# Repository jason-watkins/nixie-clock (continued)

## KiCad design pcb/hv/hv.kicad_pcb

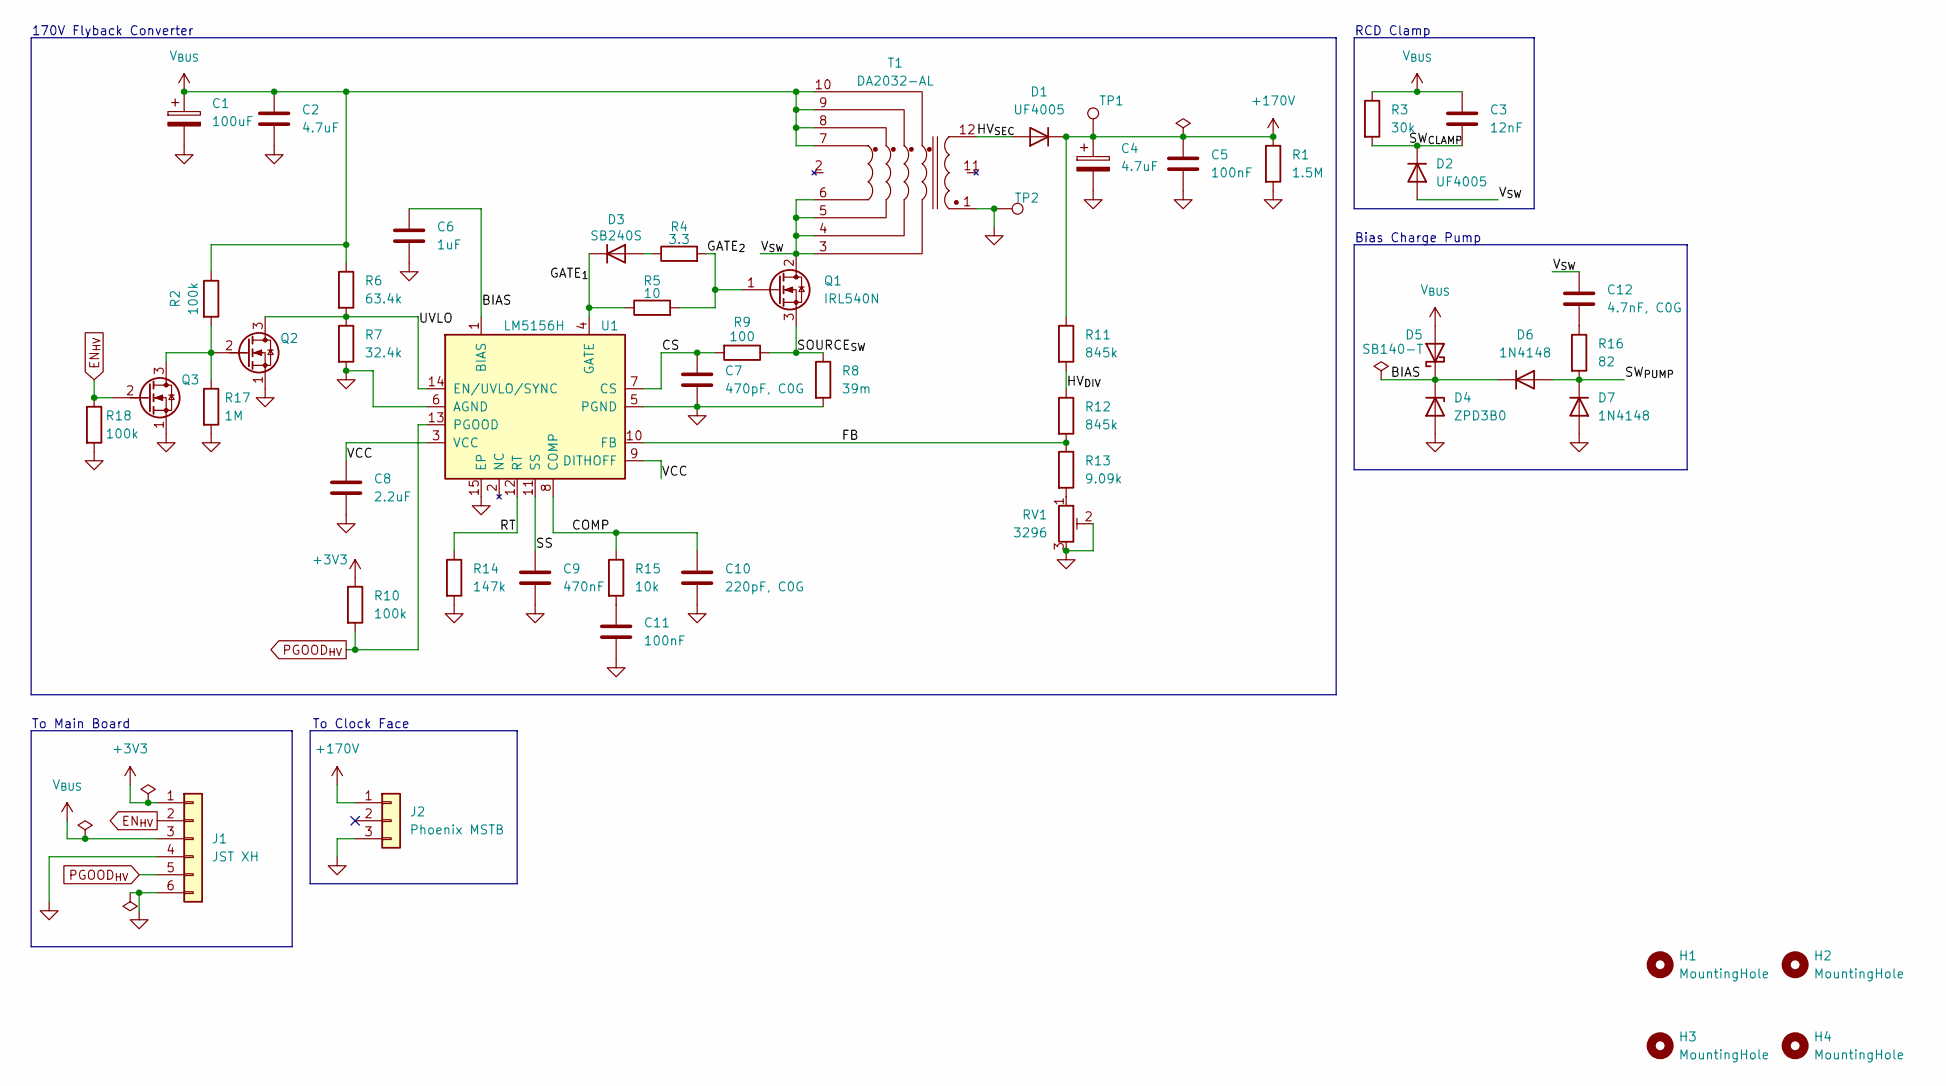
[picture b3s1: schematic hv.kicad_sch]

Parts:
C1: 100uF; CP_Radial_D8.0mm_P3.50mm; MFG Part No A750KK107M1EAAE040
C2: 4.7uF; C_Rect_L5.1mm_W3.2mm_P5.08mm_Goldmax; MFG Part No C322C475K5R5TA
C3: 12nF; C_Rect_L7.2mm_W2.5mm_P5.00mm_PHE426; MFG Part No PHE426DJ5120JR05
C4: 4.7uF; CP_Radial_D8.0mm_P3.50mm; MFG Part No A759KS475M2EAAE496
C5: 100nF; C_Rect_L7.9mm_W5.9mm_P5.00mm_ECQE; MFG Part No ECQ-E2104KB
C6: 1uF; C_Rect_L7.1mm_W4.1mm_P5.08mm_Goldmax; MFG Part No C330C105K5R5TA7303
C7: 470pF, C0G; C_Rect_L3.8mm_W2.5mm_P2.54mm_Goldmax; MFG Part No C315C471J1G5TA
C8: 2.2uF; C_Axial_L5.1mm_D3.1mm_P7.50mm_Horizontal; MFG Part No C410C225K3R5TA
C9: 470nF; C_Rect_L5.1mm_W3.2mm_P5.08mm_Goldmax; MFG Part No C322C474K5R5TA7301
C10: 220pF, C0G; C_Rect_L5.1mm_W3.2mm_P5.08mm_Goldmax; MFG Part No C322C221J2G5TA
C11: 100nF; C_Rect_L5.1mm_W3.2mm_P5.08mm_Goldmax; MFG Part No C322C104K5R5TA
C12: 4.7nF, C0G; C_Rect_L3.8mm_W2.5mm_P2.54mm_Goldmax; MFG Part No C315C472J2G5TA
D1: UF4005; D_DO-41_SOD81_P10.16mm_Horizontal; MFG Part No UF4005
D2: UF4005; D_DO-41_SOD81_P7.62mm_Horizontal; MFG Part No UF4005
D3: SB240S; D_DO-41_SOD81_P7.62mm_Horizontal; MFG Part No SB240S-E3/54
D4: ZPD3B0; D_DO-35_SOD27_P7.62mm_Horizontal; MFG Part No ZPD3B0
D5: SB140-T; D_DO-41_SOD81_P7.62mm_Horizontal; MFG Part No SB140-T
D6, D7: 1N4148; D_DO-35_SOD27_P7.62mm_Horizontal; MFG Part No 1N4148TR
H1, H2, H3, H4: MountingHole; MountingHole_3.2mm_M3_ISO7380
J1: JST XH; JST_XH_S6B-XH-A_1x06_P2.50mm_Horizontal; MFG Part No S6B-XH-A
J2: Phoenix MSTB; PhoenixContact_MSTBA_2,5_3-G-5,08_1x03_P5.08mm_Horizontal; MFG Part No 1757255
Q1: IRL540N; TO-220-3_Vertical; MFG Part No IRL540NPBF
Q2, Q3: TN2106N3-G; TO-92L; MFG Part No TN2106N3-G
R1: 1.5M; R_Axial_DIN0309_L9.0mm_D3.2mm_P12.70mm_Horizontal; MFG Part No CFR-50JB-52-1M5
R2, R10, R18: 100k; R_Axial_DIN0204_L3.6mm_D1.6mm_P5.08mm_Horizontal; MFG Part No CFR-12JB-52-100K
R3: 30k; R_Axial_DIN0207_L6.3mm_D2.5mm_P7.62mm_Horizontal; MFG Part No CFR-25JB-52-30K
R4: 3.3; R_Axial_DIN0204_L3.6mm_D1.6mm_P5.08mm_Horizontal; MFG Part No CFR-12JB-52-3R3
R5: 10; R_Axial_DIN0204_L3.6mm_D1.6mm_P5.08mm_Horizontal; MFG Part No CFR25SJT-52-10R
R6: 63.4k; R_Axial_DIN0207_L6.3mm_D2.5mm_P7.62mm_Horizontal; MFG Part No MFR-25FRF52-63K4
R7: 32.4k; R_Axial_DIN0207_L6.3mm_D2.5mm_P7.62mm_Horizontal; MFG Part No MFR-25FRF52-32K4
R8: 39m; R_2512_6332Metric_Pad1.40x3.35mm_HandSolder; MFG Part No TLRP3A20WR039FTE
R9: 100; R_Axial_DIN0204_L3.6mm_D1.6mm_P5.08mm_Horizontal; MFG Part No CFR25SJT-52-100R
R11, R12: 845k; R_Axial_DIN0207_L6.3mm_D2.5mm_P7.62mm_Horizontal; MFG Part No MFR-25FBF52-845K
R13: 9.09k; R_Axial_DIN0207_L6.3mm_D2.5mm_P7.62mm_Horizontal; MFG Part No MFR-25FBF52-9K09
R14: 147k; R_Axial_DIN0207_L6.3mm_D2.5mm_P7.62mm_Horizontal; MFG Part No MFR-25FRF52-147K
R15: 10k; R_Axial_DIN0204_L3.6mm_D1.6mm_P5.08mm_Horizontal; MFG Part No CFR-12JB-52-10K
R16: 82; R_Axial_DIN0309_L9.0mm_D3.2mm_P12.70mm_Horizontal; MFG Part No CFR-50JB-52-82R
R17: 1M; R_Axial_DIN0204_L3.6mm_D1.6mm_P5.08mm_Horizontal; MFG Part No CFR-12JB-52-1M
RV1: 3296; Potentiometer_Bourns_3296W_Vertical; MFG Part No 3296W-1-202LF
T1: DA2032-AL; MFG Part No DA2032-AL
TP1: +170V; TestPoint_Keystone_5000-5004_Miniature; MFG Part No 5001
TP2: GND; TestPoint_Keystone_5000-5004_Miniature; MFG Part No 5000
U1: LM5156H; Texas_HTSSOP-14-1EP_4.4x5mm_P0.65mm_EP3.4x5mm_Mask3.155x3.2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; MFG Part No LM51561HPWPR

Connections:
+3V3: J1.1, R10.1
+170V: C4.1, C5.1, D1.1 (K), J2.1, R1.1, R11.1, TP1.1 (1_1)
/BIAS: C6.2, D4.1 (K), D5.1 (K), D6.1 (K), U1.1 (BIAS)
/COMP: C10.2, R15.1, U1.8 (COMP)
/CS: C7.2, R9.2, U1.7 (CS)
/FB: R12.2, R13.1, U1.10 (FB)
/GATE_{1}: D3.1 (K), R5.1, U1.4 (GATE)
/GATE_{2}: Q1.1 (G), R4.2, R5.2
/HV_{DIV}: R11.2, R12.1
/HV_{SEC}: D1.2 (A), T1.12
/RT: R14.1, U1.12 (RT)
/SOURCE_{SW}: Q1.3 (S), R8.1, R9.1
/SS: C9.2, U1.11 (SS)
/SW_{CLAMP}: C3.1, D2.1 (K), R3.2
/SW_{PUMP}: D6.2 (A), D7.1 (K), R16.2
/UVLO: Q2.3 (D), R6.2, R7.1, U1.14 (EN/UVLO/SYNC)
/VCC: C8.2, U1.3 (VCC), U1.9 (DITHOFF)
/V_{SW}: C12.1, D2.2 (A), Q1.2 (D), T1.3, T1.4, T1.5, T1.6
EN_{HV}: J1.2, Q3.2 (G), R18.1
GND: C1.2, C2.2, C4.2, C5.2, C6.1, C7.1, C8.1, C9.1, C10.1, C11.1, D4.2 (A), D7.2 (A), J1.4, J1.6, J2.3, Q2.1 (S), Q3.1 (S), R1.2, R7.2, R8.2, R14.2, R17.2, R18.2, RV1.2, RV1.3, T1.1, TP2.1 (1_1), U1.5 (PGND), U1.6 (AGND), U1.15 (EP)
unnamed: C11.2, R15.2
unnamed: C12.2, R16.1
unnamed: D3.2 (A), R4.1
unnamed: Q2.2 (G), Q3.3 (D), R2.2, R17.1
unnamed: R13.2, RV1.1
PGOOD_{HV}: J1.5, R10.2, U1.13 (PGOOD)
V_{BUS}: C1.1, C2.1, C3.2, D5.2 (A), J1.3, R2.1, R3.1, R6.1, T1.7, T1.8, T1.9, T1.10

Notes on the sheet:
To Main Board
To Clock Face
Bias Charge Pump
RCD Clamp
170V Flyback Converter

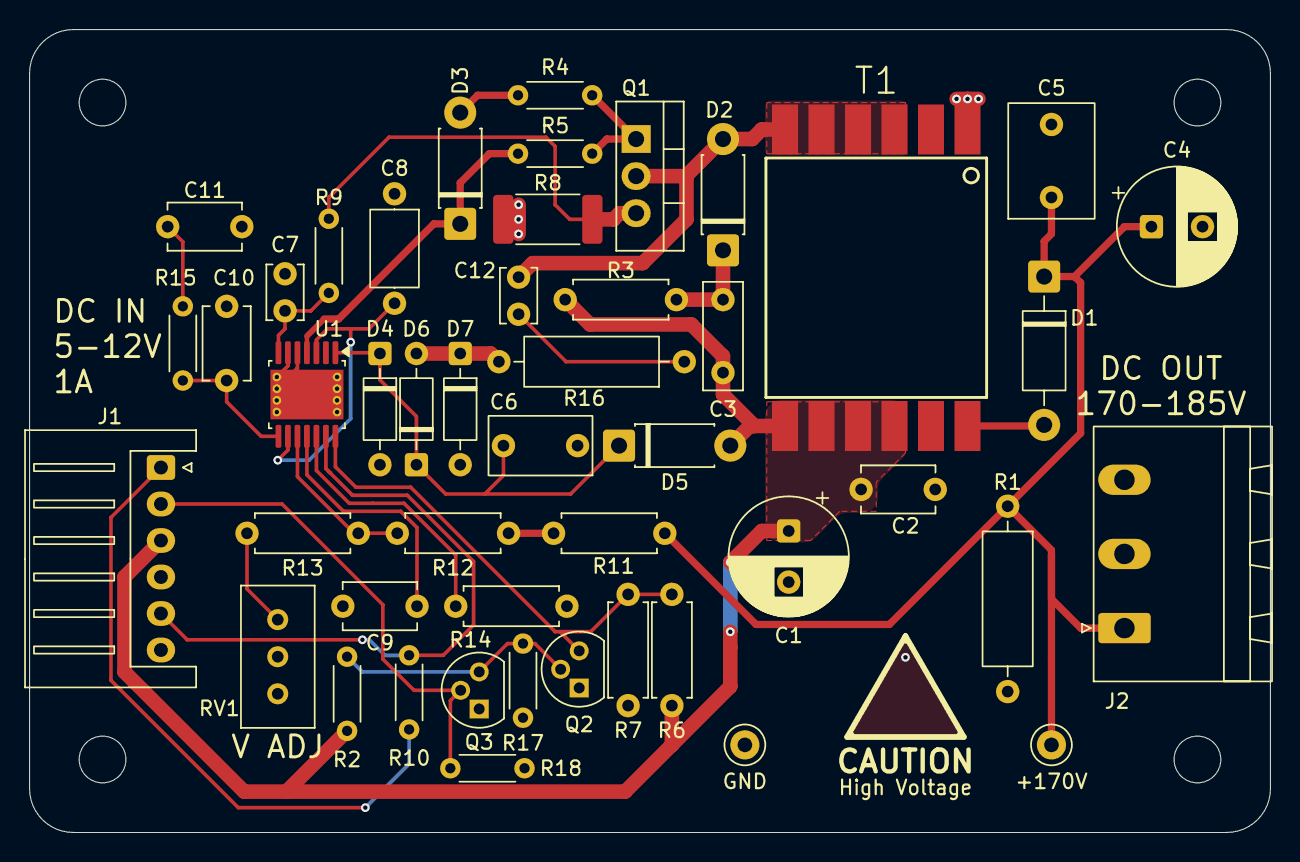
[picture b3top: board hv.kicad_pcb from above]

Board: 2 copper layers, 85.0 x 55.0 mm, 51 parts (0 on the bottom side), 27 nets.

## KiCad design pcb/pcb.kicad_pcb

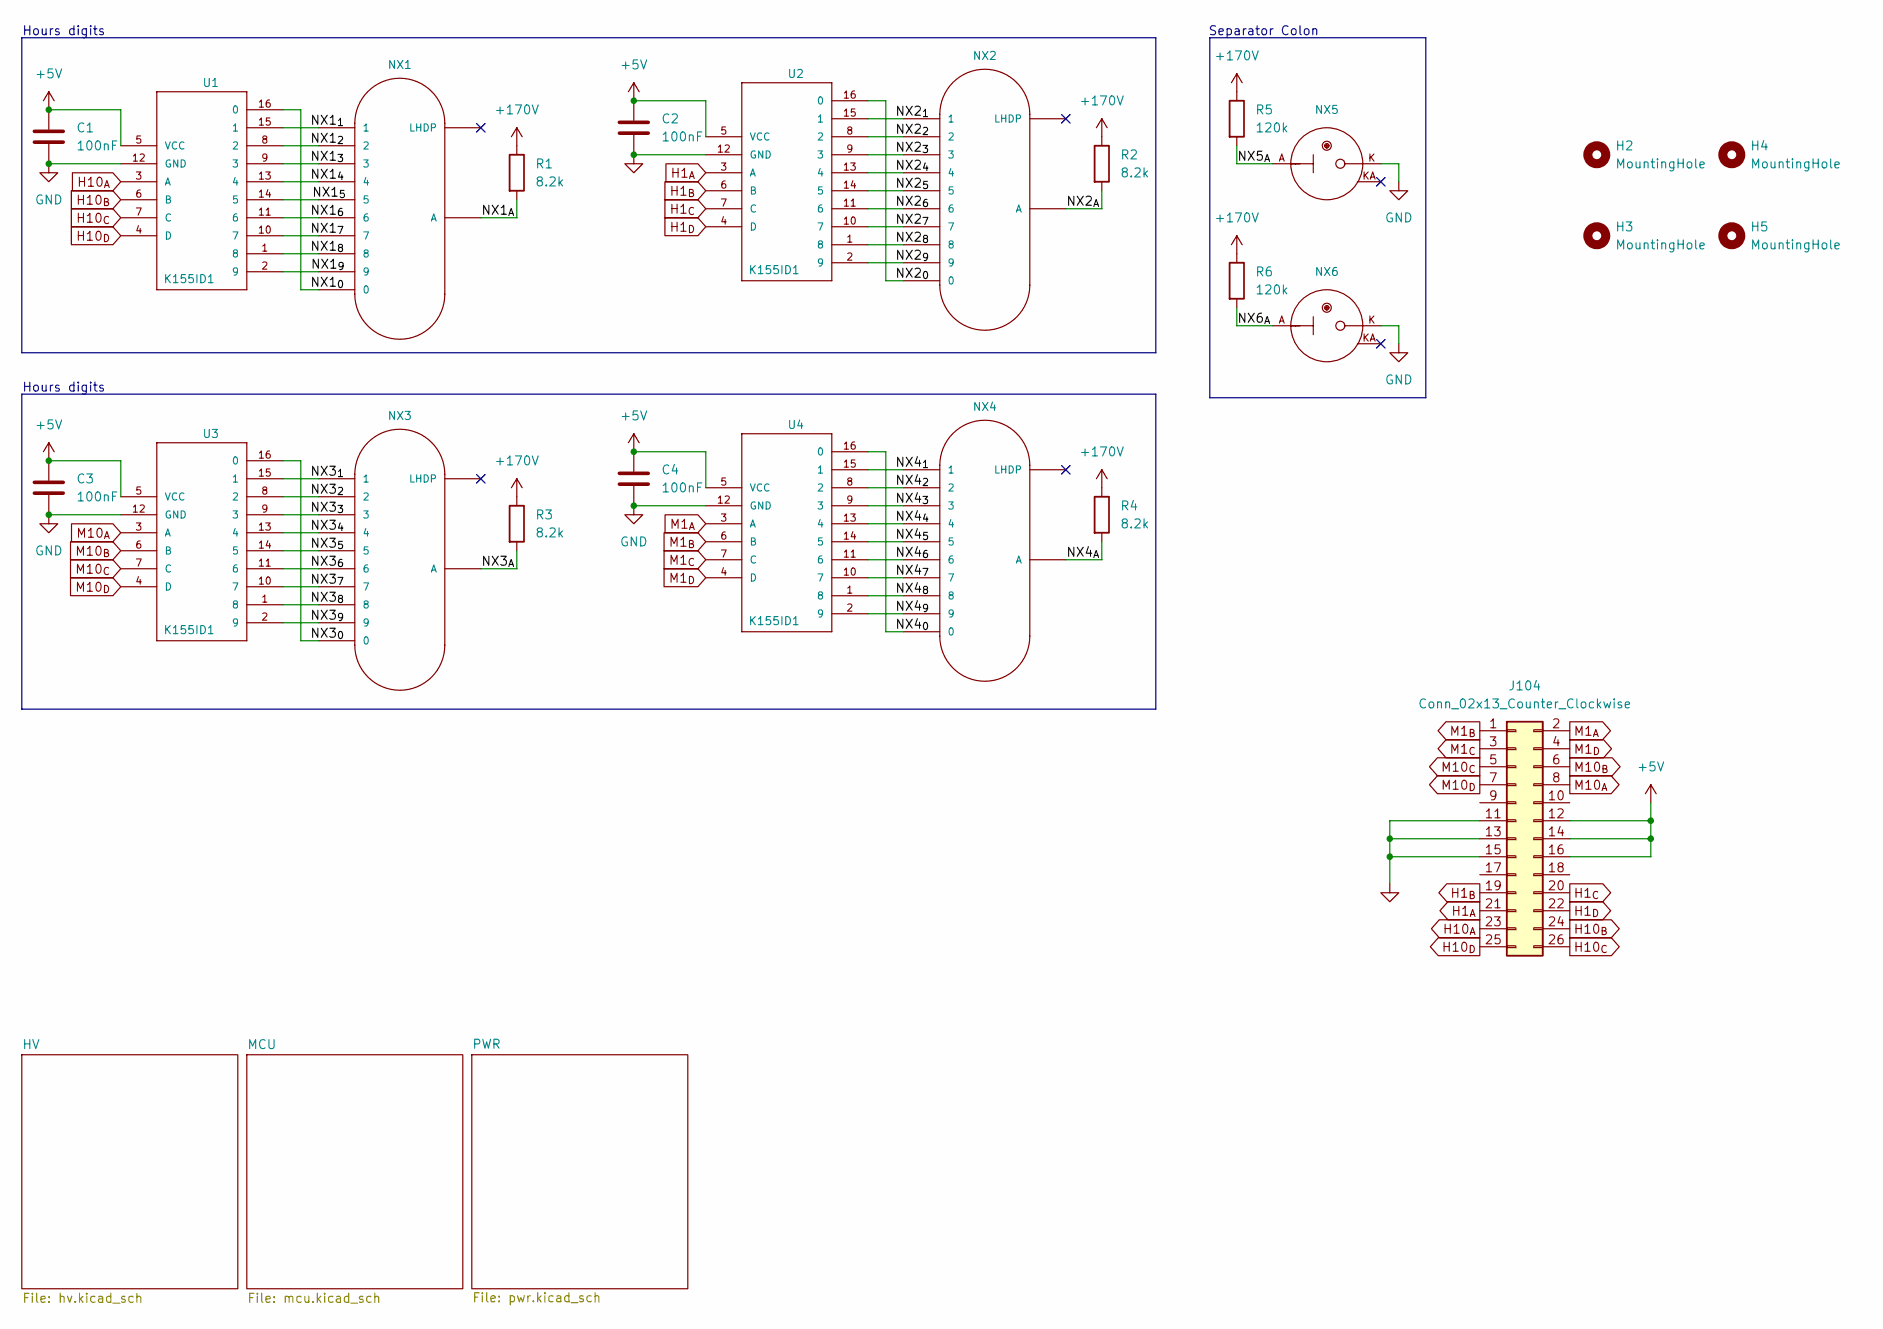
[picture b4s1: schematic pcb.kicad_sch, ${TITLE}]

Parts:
C1, C2, C3, C4: 100nF; C_Rect_L5.1mm_W3.2mm_P2.54mm_Goldmax; MFG Part No C320C104K5R5TA
H2, H3, H4, H5: MountingHole; MountingHole_3.2mm_M3_ISO7380
J104: Conn_02x13_Counter_Clockwise; IDC-Header_2x13_P2.54mm_Vertical
NX1, NX2, NX3, NX4: IN-12B; IN-12-DSUB
NX5, NX6: IN-6
R1, R2, R3, R4: 8.2k; R_Axial_DIN0207_L6.3mm_D2.5mm_P10.16mm_Horizontal; MFG Part No MFR-25FTE52-8K2
R5, R6: 120k; R_Axial_DIN0207_L6.3mm_D2.5mm_P10.16mm_Horizontal; MFG Part No MFR-25FRF52-120K
U1, U2, U3, U4: K155ID1; DIP16

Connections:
+5V: C1.1, C2.1, C3.1, C4.1, J104.12, J104.14, J104.16, U1.5 (VCC), U2.5 (VCC), U3.5 (VCC), U4.5 (VCC); also elsewhere on the board
+170V: R1.1, R2.1, R3.1, R4.1, R5.1, R6.1; also elsewhere on the board
/NX1_{0}: NX1.0, U1.16 (0)
/NX1_{1}: NX1.1, U1.15 (1)
/NX1_{2}: NX1.2, U1.8 (2)
/NX1_{3}: NX1.3, U1.9 (3)
/NX1_{4}: NX1.4, U1.13 (4)
/NX1_{5}: NX1.5, U1.14 (5)
/NX1_{6}: NX1.6, U1.11 (6)
/NX1_{7}: NX1.7, U1.10 (7)
/NX1_{8}: NX1.8, U1.1 (8)
/NX1_{9}: NX1.9, U1.2 (9)
/NX1_{A}: NX1.A, R1.2
/NX2_{0}: NX2.0, U2.16 (0)
/NX2_{1}: NX2.1, U2.15 (1)
/NX2_{2}: NX2.2, U2.8 (2)
/NX2_{3}: NX2.3, U2.9 (3)
/NX2_{4}: NX2.4, U2.13 (4)
/NX2_{5}: NX2.5, U2.14 (5)
/NX2_{6}: NX2.6, U2.11 (6)
/NX2_{7}: NX2.7, U2.10 (7)
/NX2_{8}: NX2.8, U2.1 (8)
/NX2_{9}: NX2.9, U2.2 (9)
/NX2_{A}: NX2.A, R2.2
/NX3_{0}: NX3.0, U3.16 (0)
/NX3_{1}: NX3.1, U3.15 (1)
/NX3_{2}: NX3.2, U3.8 (2)
/NX3_{3}: NX3.3, U3.9 (3)
/NX3_{4}: NX3.4, U3.13 (4)
/NX3_{5}: NX3.5, U3.14 (5)
/NX3_{6}: NX3.6, U3.11 (6)
/NX3_{7}: NX3.7, U3.10 (7)
/NX3_{8}: NX3.8, U3.1 (8)
/NX3_{9}: NX3.9, U3.2 (9)
/NX3_{A}: NX3.A, R3.2
/NX4_{0}: NX4.0, U4.16 (0)
/NX4_{1}: NX4.1, U4.15 (1)
/NX4_{2}: NX4.2, U4.8 (2)
/NX4_{3}: NX4.3, U4.9 (3)
/NX4_{4}: NX4.4, U4.13 (4)
/NX4_{5}: NX4.5, U4.14 (5)
/NX4_{6}: NX4.6, U4.11 (6)
/NX4_{7}: NX4.7, U4.10 (7)
/NX4_{8}: NX4.8, U4.1 (8)
/NX4_{9}: NX4.9, U4.2 (9)
/NX4_{A}: NX4.A, R4.2
/NX5_{A}: NX5.A, R5.2
/NX6_{A}: NX6.A, R6.2
GND: C1.2, C2.2, C3.2, C4.2, J104.11, J104.13, J104.15, NX5.K, NX6.K, U1.12 (GND), U2.12 (GND), U3.12 (GND), U4.12 (GND); also elsewhere on the board
H1_{A}: J104.21, U2.3 (A); also elsewhere on the board
H1_{B}: J104.19, U2.6 (B); also elsewhere on the board
H1_{C}: J104.20, U2.7 (C); also elsewhere on the board
H1_{D}: J104.22, U2.4 (D); also elsewhere on the board
H10_{A}: J104.23, U1.3 (A); also elsewhere on the board
H10_{B}: J104.24, U1.6 (B); also elsewhere on the board
H10_{C}: J104.26, U1.7 (C); also elsewhere on the board
H10_{D}: J104.25, U1.4 (D); also elsewhere on the board
M1_{A}: J104.2, U4.3 (A); also elsewhere on the board
M1_{B}: J104.1, U4.6 (B); also elsewhere on the board
M1_{C}: J104.3, U4.7 (C); also elsewhere on the board
M1_{D}: J104.4, U4.4 (D); also elsewhere on the board
M10_{A}: J104.8, U3.3 (A); also elsewhere on the board
M10_{B}: J104.6, U3.6 (B); also elsewhere on the board
M10_{C}: J104.5, U3.7 (C); also elsewhere on the board
M10_{D}: J104.7, U3.4 (D); also elsewhere on the board

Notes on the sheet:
Hours digits
Separator Colon

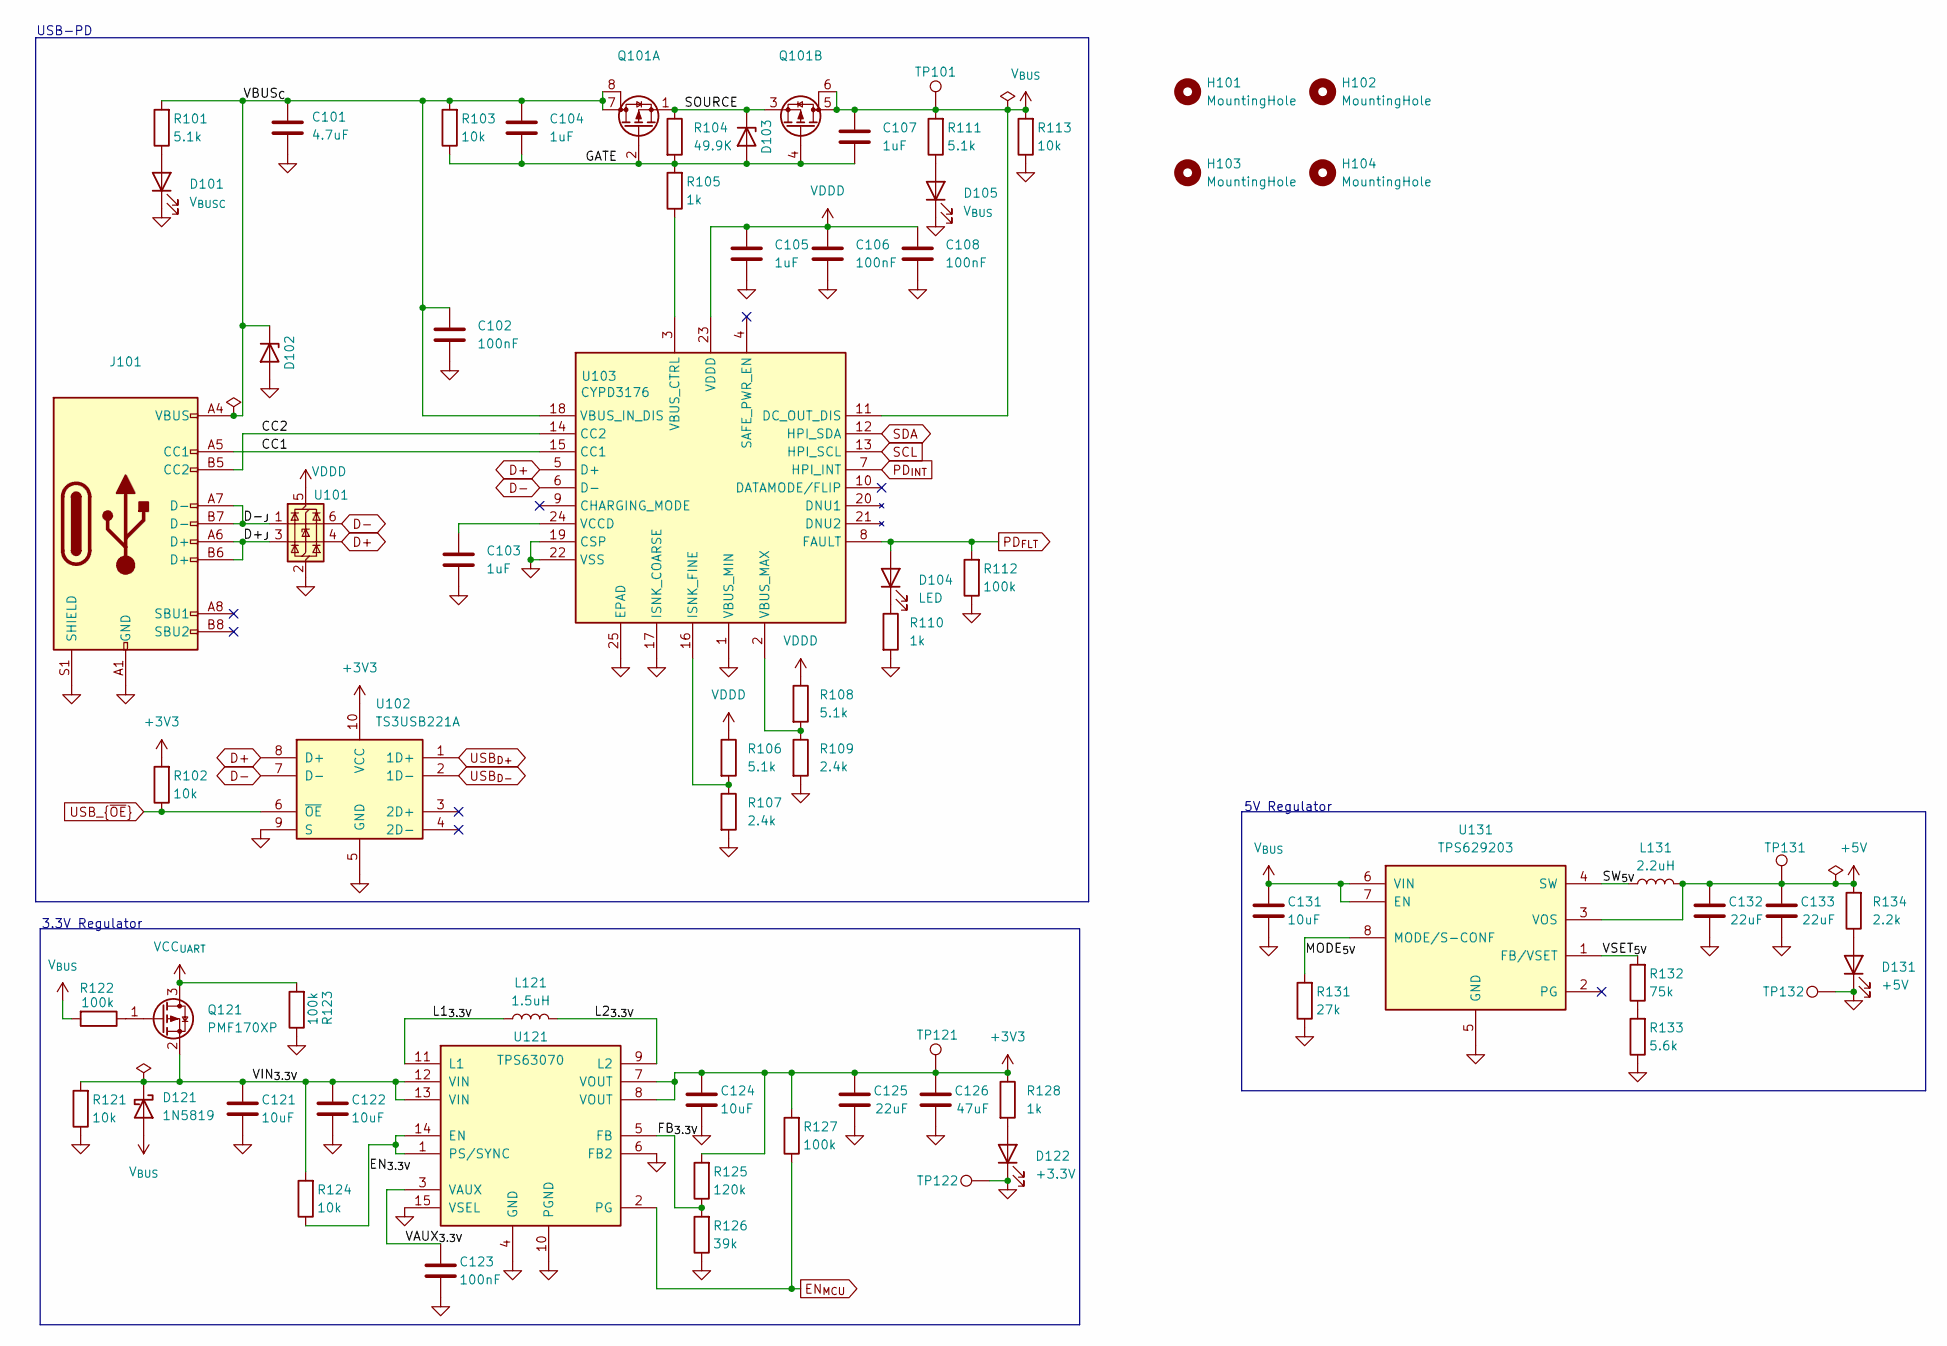
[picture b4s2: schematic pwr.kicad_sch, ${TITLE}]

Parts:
C101: 4.7uF; C_0805_2012Metric_Pad1.18x1.45mm_HandSolder; MFG Part No CL21A475KAQNNNE; LCSC C1779
C102: 100nF; C_0402_1005Metric; MFG Part No CL05B104KB54PNC; LCSC C307331
C103, C104, C105, C107: 1uF; C_0402_1005Metric; MFG Part No CL05A105KA5NQNC; LCSC C52923
C106, C108, C123: 100nF; C_0402_1005Metric; MFG Part No CL05B104KO5NNNC; LCSC C1525
C121, C131: 10uF; C_0805_2012Metric; MFG Part No CL21A106KAYNNNE; LCSC C15850
C122: 10uF; C_0603_1608Metric; MFG Part No CL10A106MA8NRNC; LCSC C96446
C124: 10uF; C_0603_1608Metric; MFG Part No CL10A226MQ8NRNC; LCSC C59461
C125, C132, C133: 22uF; C_1206_3216Metric; MFG Part No CL31A226KPHNNNE; LCSC C5672
C126: 47uF; C_1206_3216Metric; MFG Part No CL31A476MPHNNNE; LCSC C96123
D101: V_{BUSC}; LED_0603_1608Metric; MFG Part No KT-0603R; LCSC C2286
D102: SD15Q-7; D_SOD-323; MFG Part No SD15Q-7; LCSC C19950473
D103: MM3Z10VST1G; D_SOD-323_HandSoldering; MFG Part No MM3Z10VST1G
D104: LED; LED_0603_1608Metric; MFG Part No KT-0603R; LCSC C2286
D105: V_{BUS}; LED_0603_1608Metric; MFG Part No KT-0603R; LCSC C2286
D121: 1N5819; D_SOD-123; MFG Part No 1N5819HW-7-F
D122: +3.3V; LED_0603_1608Metric; MFG Part No KT-0603R; LCSC C2286
D131: +5V; LED_0603_1608Metric; MFG Part No KT-0603R; LCSC C2286
H101, H102, H103, H104: MountingHole; MountingHole_3.2mm_M3_ISO7380
J101: USB_C_Receptacle_USB2.0_16P; USB_C_Receptacle_JAE_DX07S016JA1R1500; MFG Part No DX07S016JA1R1500
L121: 1.5uH; L_Bourns_SRN5040TA; MFG Part No SRN5040TA-1R5M
L131: 2.2uH; L_Bourns_SRN5040TA; MFG Part No SRN5040TA-2R2M
Q101: Q_Dual_PMOS_S1G1S2G2D2D2D1D1; SOIC-8_3.9x4.9mm_P1.27mm; MFG Part No DMP3085LSD-13
Q121: PMF170XP; SOT-323_SC-70; MFG Part No PMF170XP,115
R101, R111: 5.1k; R_0603_1608Metric; MFG Part No 0603WAF5101T5E; LCSC C23186
R102, R103, R113, R121, R124: 10k; R_0402_1005Metric; MFG Part No 0402WGF1002TCE; LCSC C25744
R104: 49.9K; R_0402_1005Metric; MFG Part No 0402WGF4992TCE; LCSC C25897
R105: 1k; R_0402_1005Metric; MFG Part No 0402WGF1002TCE; LCSC C11702
R106, R108: 5.1k; R_0402_1005Metric; MFG Part No 0402WGF5101TCE; LCSC C25905
R107, R109: 2.4k; R_0402_1005Metric; MFG Part No 0402WGF5101TCE; LCSC C25905
R110, R128: 1k; R_0402_1005Metric; MFG Part No 0402WGF1001TCE; LCSC C11702
R112, R122, R123, R127: 100k; R_0402_1005Metric; MFG Part No 0402WGF1003TCE; LCSC C25741
R125: 120k; R_0402_1005Metric; MFG Part No 0402WGF1203TCE; LCSC C25750
R126: 39k; R_0402_1005Metric; MFG Part No 0402WGF5102TCE; LCSC C25794
R131: 27k; R_0402_1005Metric; MFG Part No 0402WGF2702TCE; LCSC C25771
R132: 75k; R_0402_1005Metric; MFG Part No 0402WGF7502TCE; LCSC C25798
R133: 5.6k; R_0402_1005Metric; MFG Part No 0402WGF5601TCE; LCSC C25908
R134: 2.2k; R_0402_1005Metric; MFG Part No 0402WGF2201TCE; LCSC C25879
TP101: V_{BUS}; TestPoint_Pad_D1.0mm
TP121: +3V3; TestPoint_Pad_D1.0mm
TP122, TP132: GND; TestPoint_Pad_D1.0mm
TP131: +5V; TestPoint_Pad_D1.0mm
U101: USBLC6-2SC6; SOT-23-6; MFG Part No USBLC6-2SC6; LCSC C7519
U102: TS3USB221A; UQFN-10_1.5x2mm_P0.5mm_TI_RSE0010A
U103: CYPD3176; QFN-24-1EP_4x4mm_P0.5mm_EP2.75x2.75mm_ThermalVias; MFG Part No CYPD3176-24LQXQ
U121: TPS63070; VQFN-15_2.5x3mm_TI_RNM0015A; MFG Part No TPS630702RNMR
U131: TPS629203; SOT-583-8; MFG Part No TPS629203DRLR

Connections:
+3V3: C124.1, C125.1, C126.1, R102.2, R125.2, R127.2, R128.1, TP121.1, U102.10 (VCC), U121.7 (VOUT), U121.8 (VOUT); also elsewhere on the board
+5V: C132.1, C133.1, L131.2, R134.2, TP131.1, U131.3 (VOS); also elsewhere on the board
/PWR/CC1: J101.A5 (CC1), U103.15 (CC1)
/PWR/CC2: J101.B5 (CC2), U103.14 (CC2)
/PWR/D+_{J}: J101.A6 (D+), J101.B6 (D+), U101.3 (I/O2)
/PWR/D-_{J}: J101.A7 (D-), J101.B7 (D-), U101.1 (I/O1)
/PWR/EN_{3.3V}: R124.1, U121.1 (PS/SYNC), U121.14 (EN)
/PWR/FB_{3.3V}: R125.1, R126.2, U121.5 (FB)
/PWR/GATE: C104.2, C107.2, D103.2 (A), Q101.2 (G), Q101.4 (G), R103.1, R104.2, R105.2
/PWR/L1_{3.3V}: L121.1, U121.11 (L1)
/PWR/L2_{3.3V}: L121.2, U121.9 (L2)
/PWR/MODE_{5V}: R131.2, U131.8 (MODE/S-CONF)
/PWR/SOURCE: D103.1 (K), Q101.1 (S), Q101.3 (S), R104.1
/PWR/SW_{5V}: L131.1, U131.4 (SW)
/PWR/VAUX_{3.3V}: C123.1, U121.3 (VAUX)
/PWR/VBUS_{C}: C101.1, C102.1, C104.1, D102.1 (K), J101.A4 (VBUS), J101.A9 (VBUS), J101.B4 (VBUS), J101.B9 (VBUS), Q101.7 (D), Q101.8 (D), R101.2, R103.2, U103.18 (VBUS_IN_DIS)
/PWR/VIN_{3.3V}: C121.1, C122.1, D121.1 (K), Q121.2 (S), R121.2, R124.2, U121.12 (VIN), U121.13 (VIN)
/PWR/VSET_{5V}: R132.2, U131.1 (FB/VSET)
D+: U101.4 (I/O2), U102.8 (D+), U103.5 (D+)
D-: U101.6 (I/O1), U102.7 (D-), U103.6 (D-)
EN_{MCU}: R127.1, U121.2 (PG); also elsewhere on the board
GND: C101.2, C102.2, C103.2, C105.2, C106.2, C108.2, C121.2, C122.2, C123.2, C124.2, C125.2, C126.2, C131.2, C132.2, C133.2, D101.1 (K), D102.2 (A), D105.1 (K), D122.1 (K), D131.1 (K), J101.A1 (GND), J101.A12 (GND), J101.B1 (GND), J101.B12 (GND), J101.S1 (SHIELD), R107.2, R109.2, R110.2, R112.1, R113.1, R121.1, R123.1, R126.1, R131.1, R133.1, TP122.1, TP132.1, U101.2 (GND), U102.5 (GND), U102.9 (S), U103.1 (VBUS_MIN), U103.17 (ISNK_COARSE), U103.19 (CSP), U103.22 (VSS), U103.25 (EPAD), U121.4 (GND), U121.6 (FB2), U121.10 (PGND), U121.15 (VSEL), U131.5 (GND); also elsewhere on the board
unnamed: D101.2 (A), R101.1
unnamed: D104.1 (K), R110.1
unnamed: D105.2 (A), R111.1
unnamed: D122.2 (A), R128.2
unnamed: D131.2 (A), R134.1
unnamed: Q121.1 (G), R122.1
unnamed: R132.1, R133.2
unnamed: R106.2, R107.1, U103.16 (ISNK_FINE)
unnamed: R105.1, U103.3 (VBUS_CTRL)
unnamed: R108.2, R109.1, U103.2 (VBUS_MAX)
unnamed: C103.1, U103.24 (VCCD)
PD_{FLT}: D104.2 (A), R112.2, U103.8 (FAULT); also elsewhere on the board
PD_{INT}: U103.7 (HPI_INT); also elsewhere on the board
SCL: U103.13 (HPI_SCL); also elsewhere on the board
SDA: U103.12 (HPI_SDA); also elsewhere on the board
USB_{D+}: U102.1 (1D+); also elsewhere on the board
USB_{D-}: U102.2 (1D-); also elsewhere on the board
USB_{~OE}: R102.1, U102.6 (~OE); also elsewhere on the board
VCC_{UART}: Q121.3 (D), R123.2; also elsewhere on the board
VDDD: C105.1, C106.1, C108.1, R106.1, R108.1, U101.5 (VBUS), U103.23 (VDDD)
V_{BUS}: C107.1, C131.1, D121.2 (A), Q101.5 (D), Q101.6 (D), R111.2, R113.2, R122.2, TP101.1, U103.11 (DC_OUT_DIS), U131.6 (VIN), U131.7 (EN); also elsewhere on the board

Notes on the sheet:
USB-PD
5V Regulator
3.3V Regulator

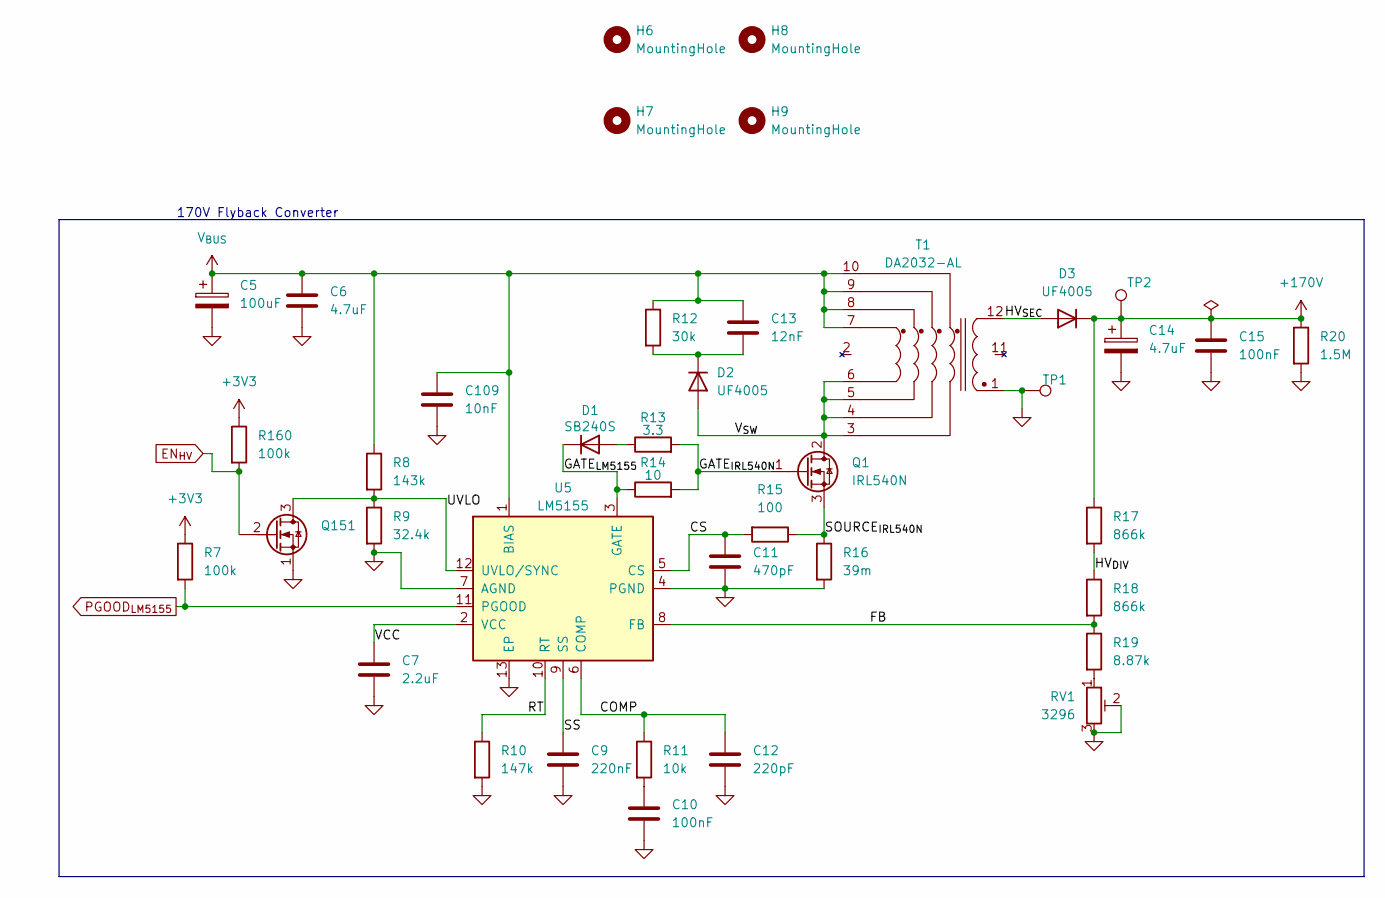
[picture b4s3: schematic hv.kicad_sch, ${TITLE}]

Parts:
C5: 100uF; CP_Radial_D8.0mm_P3.50mm; MFG Part No A750KK107M1EAAE040
C6: 4.7uF; C_Rect_L5.1mm_W3.2mm_P5.08mm_Goldmax; MFG Part No C322C475K5R5TA
C7: 2.2uF; C_Rect_L5.1mm_W3.2mm_P5.08mm_Goldmax; MFG Part No C322C225K5R5TA
C9: 220nF; C_Rect_L5.1mm_W3.2mm_P5.08mm_Goldmax; MFG Part No C322C224K5R5TA7301
C10: 100nF; C_Rect_L5.1mm_W3.2mm_P5.08mm_Goldmax; MFG Part No C322C104K5R5TA
C11: 470pF; C_Rect_L3.8mm_W2.5mm_P2.54mm_Goldmax; MFG Part No C315C471K5R5TA
C12: 220pF; C_Rect_L5.1mm_W3.2mm_P5.08mm_Goldmax; MFG Part No C322C221K5R5TA
C13: 12nF; C_Rect_L3.8mm_W2.5mm_P5.08mm_Goldmax; MFG Part No C317C123K1R5TA7301
C14: 4.7uF; CP_Radial_D8.0mm_P3.50mm; MFG Part No A759KS475M2EAAE496
C15: 100nF; C_Rect_L7.9mm_W5.9mm_P5.00mm_ECQE; MFG Part No ECQ-E2104KB
C109: 10nF; C_Rect_L5.1mm_W3.2mm_P5.08mm_Goldmax; MFG Part No C322C103K5R5TA
D1: SB240S; D_DO-41_SOD81_P7.62mm_Horizontal; MFG Part No SB240S-E3/54
D2: UF4005; D_DO-41_SOD81_P7.62mm_Horizontal; MFG Part No UF4005
D3: UF4005; D_DO-41_SOD81_P10.16mm_Horizontal; MFG Part No UF4005
H6, H7, H8, H9: MountingHole; MountingHole_3.2mm_M3_ISO7380
Q1: IRL540N; TO-220-3_Vertical; MFG Part No IRL540NPBF
Q151: TN2106N3-G; TO-92L; MFG Part No TN2106N3-G
R7, R160: 100k; R_Axial_DIN0207_L6.3mm_D2.5mm_P7.62mm_Horizontal; MFG Part No MFR-25FRF52-100K
R8: 143k; R_Axial_DIN0207_L6.3mm_D2.5mm_P7.62mm_Horizontal; MFG Part No MFR-25FRF52-143K
R9: 32.4k; R_Axial_DIN0207_L6.3mm_D2.5mm_P7.62mm_Horizontal; MFG Part No MFR-25FRF52-32K4
R10: 147k; R_Axial_DIN0207_L6.3mm_D2.5mm_P7.62mm_Horizontal; MFG Part No MFR-25FRF52-147K
R11: 10k; R_Axial_DIN0207_L6.3mm_D2.5mm_P7.62mm_Horizontal; MFG Part No MFR-25FRF52-10K
R12: 30k; R_Axial_DIN0207_L6.3mm_D2.5mm_P7.62mm_Horizontal; MFG Part No MFR-25FRF52-30K
R13: 3.3; R_Axial_DIN0207_L6.3mm_D2.5mm_P7.62mm_Horizontal; MFG Part No MFR-25FTE52-3R3
R14: 10; R_Axial_DIN0207_L6.3mm_D2.5mm_P7.62mm_Horizontal; MFG Part No MFR-25FBF52-10R
R15: 100; R_Axial_DIN0207_L6.3mm_D2.5mm_P7.62mm_Horizontal; MFG Part No MFR-25FBF52-100R
R16: 39m; R_2512_6332Metric_Pad1.40x3.35mm_HandSolder; MFG Part No TLRP3A20WR039FTE
R17, R18: 866k; R_Axial_DIN0207_L6.3mm_D2.5mm_P7.62mm_Horizontal; MFG Part No MFR-25FRF52-866K
R19: 8.87k; R_Axial_DIN0207_L6.3mm_D2.5mm_P7.62mm_Horizontal; MFG Part No MFR-25FBF52-8K87
R20: 1.5M; R_Axial_DIN0207_L6.3mm_D2.5mm_P7.62mm_Horizontal; MFG Part No MFR-25FBF52-1M5
RV1: 3296; Potentiometer_Bourns_3296W_Vertical; MFG Part No 3296W-1-202LF
T1: DA2032-AL; MFG Part No DA2032-AL
TP1: GND; TestPoint_Keystone_5000-5004_Miniature; MFG Part No 5000
TP2: +170V; TestPoint_Keystone_5000-5004_Miniature; MFG Part No 5001
U5: LM5155; WSON-12-1EP_3x2mm_P0.5mm_EP1x2.65_ThermalVias; MFG Part No LM51551DSSR

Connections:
+3V3: R7.1, R160.1; also elsewhere on the board
+170V: C14.1, C15.1, D3.1 (K), R17.1, R20.1, TP2.1; also elsewhere on the board
/HV/COMP: C12.2, R11.1, U5.6 (COMP)
/HV/CS: C11.2, R15.2, U5.5 (CS)
/HV/FB: R18.2, R19.1, U5.8 (FB)
/HV/GATE_{IRL540N}: Q1.1 (G), R13.2, R14.2
/HV/GATE_{LM5155}: D1.1 (K), R14.1, U5.3 (GATE)
/HV/HV_{DIV}: R17.2, R18.1
/HV/HV_{SEC}: D3.2 (A), T1.12
/HV/RT: R10.1, U5.10 (RT)
/HV/SOURCE_{IRL540N}: Q1.3 (S), R15.1, R16.1
/HV/SS: C9.2, U5.9 (SS)
/HV/UVLO: Q151.3 (D), R8.2, R9.1, U5.12 (UVLO/SYNC)
/HV/VCC: C7.2, U5.2 (VCC)
/HV/V_{SW}: D2.2 (A), Q1.2 (D), T1.3, T1.4, T1.5, T1.6
EN_{HV}: Q151.2 (G), R160.2; also elsewhere on the board
GND: C5.2, C6.2, C7.1, C9.1, C10.1, C11.1, C12.1, C14.2, C15.2, C109.1, Q151.1 (S), R9.2, R10.2, R16.2, R20.2, RV1.2, RV1.3, T1.1, TP1.1, U5.4 (PGND), U5.7 (AGND), U5.13 (EP); also elsewhere on the board
unnamed: C10.2, R11.2
unnamed: D1.2 (A), R13.1
unnamed: C13.1, D2.1 (K), R12.2
unnamed: R19.2, RV1.1
PGOOD_{LM5155}: R7.2, U5.11 (PGOOD); also elsewhere on the board
V_{BUS}: C5.1, C6.1, C13.2, C109.2, R8.1, R12.1, T1.7, T1.8, T1.9, T1.10, U5.1 (BIAS); also elsewhere on the board

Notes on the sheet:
170V Flyback Converter
